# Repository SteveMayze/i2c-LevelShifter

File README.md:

# i2c-LevelShifter
A small project to design and implement a simple level shifter for an I2C bus.

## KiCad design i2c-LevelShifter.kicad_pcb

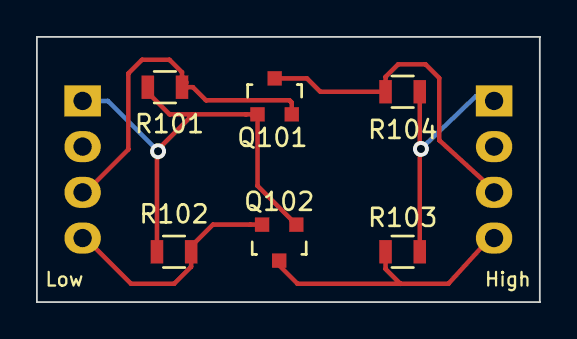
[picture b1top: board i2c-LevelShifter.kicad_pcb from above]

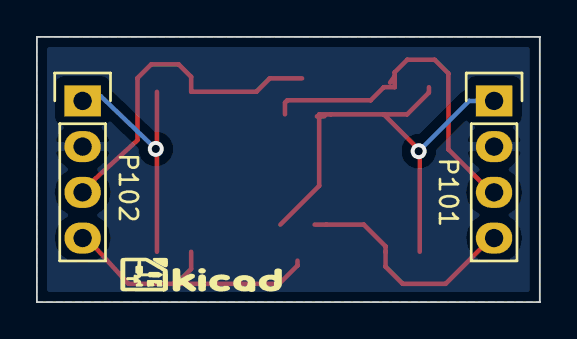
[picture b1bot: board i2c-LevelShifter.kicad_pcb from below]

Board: 2 copper layers, 27.9 x 14.7 mm, 8 parts (2 on the bottom side), 7 nets.

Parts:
P101: 3v3; Pin_Header_Straight_1x04
P102: 5v; Pin_Header_Straight_1x04
Q101, Q102: IRLML2502; SOT-23
R101, R102: 10k; R_0805
R103, R104: 1k5; R_0805

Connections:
/SCL1: P101.4, Q102.2, R102.2
/SCL2: P102.4, Q102.3, R103.2
/SDA1: P101.3, Q101.2, R101.2
/SDA2: P102.3, Q101.3, R104.2
/VDD1=3v3: P101.1, Q101.1, Q102.1, R101.1, R102.1
/VSS2=5v: P102.1, R103.1, R104.1
GND: P101.2, P102.2

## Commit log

2015-03-10 An initial checkin for the i2c level shifter project
2015-03-10 Created the empty Schema
2015-03-11 Added new part and created initial schematic
2015-03-11 Added connectors to the schematic
2015-03-12 Added ltspice model and annotated the schema with the calculations
2015-03-16 Added MPN to the template field names
2015-03-16 Completed layout and Gerber files
2015-03-19 Corrected lib reference
2015-03-20 New board layout and kiCad logo
2015-03-21 Corrected layout for P102 board edge
2015-03-31 corrected wires to small components after default symbol change
2015-04-08 Changed the layout footprint to more suitable for Bread board
